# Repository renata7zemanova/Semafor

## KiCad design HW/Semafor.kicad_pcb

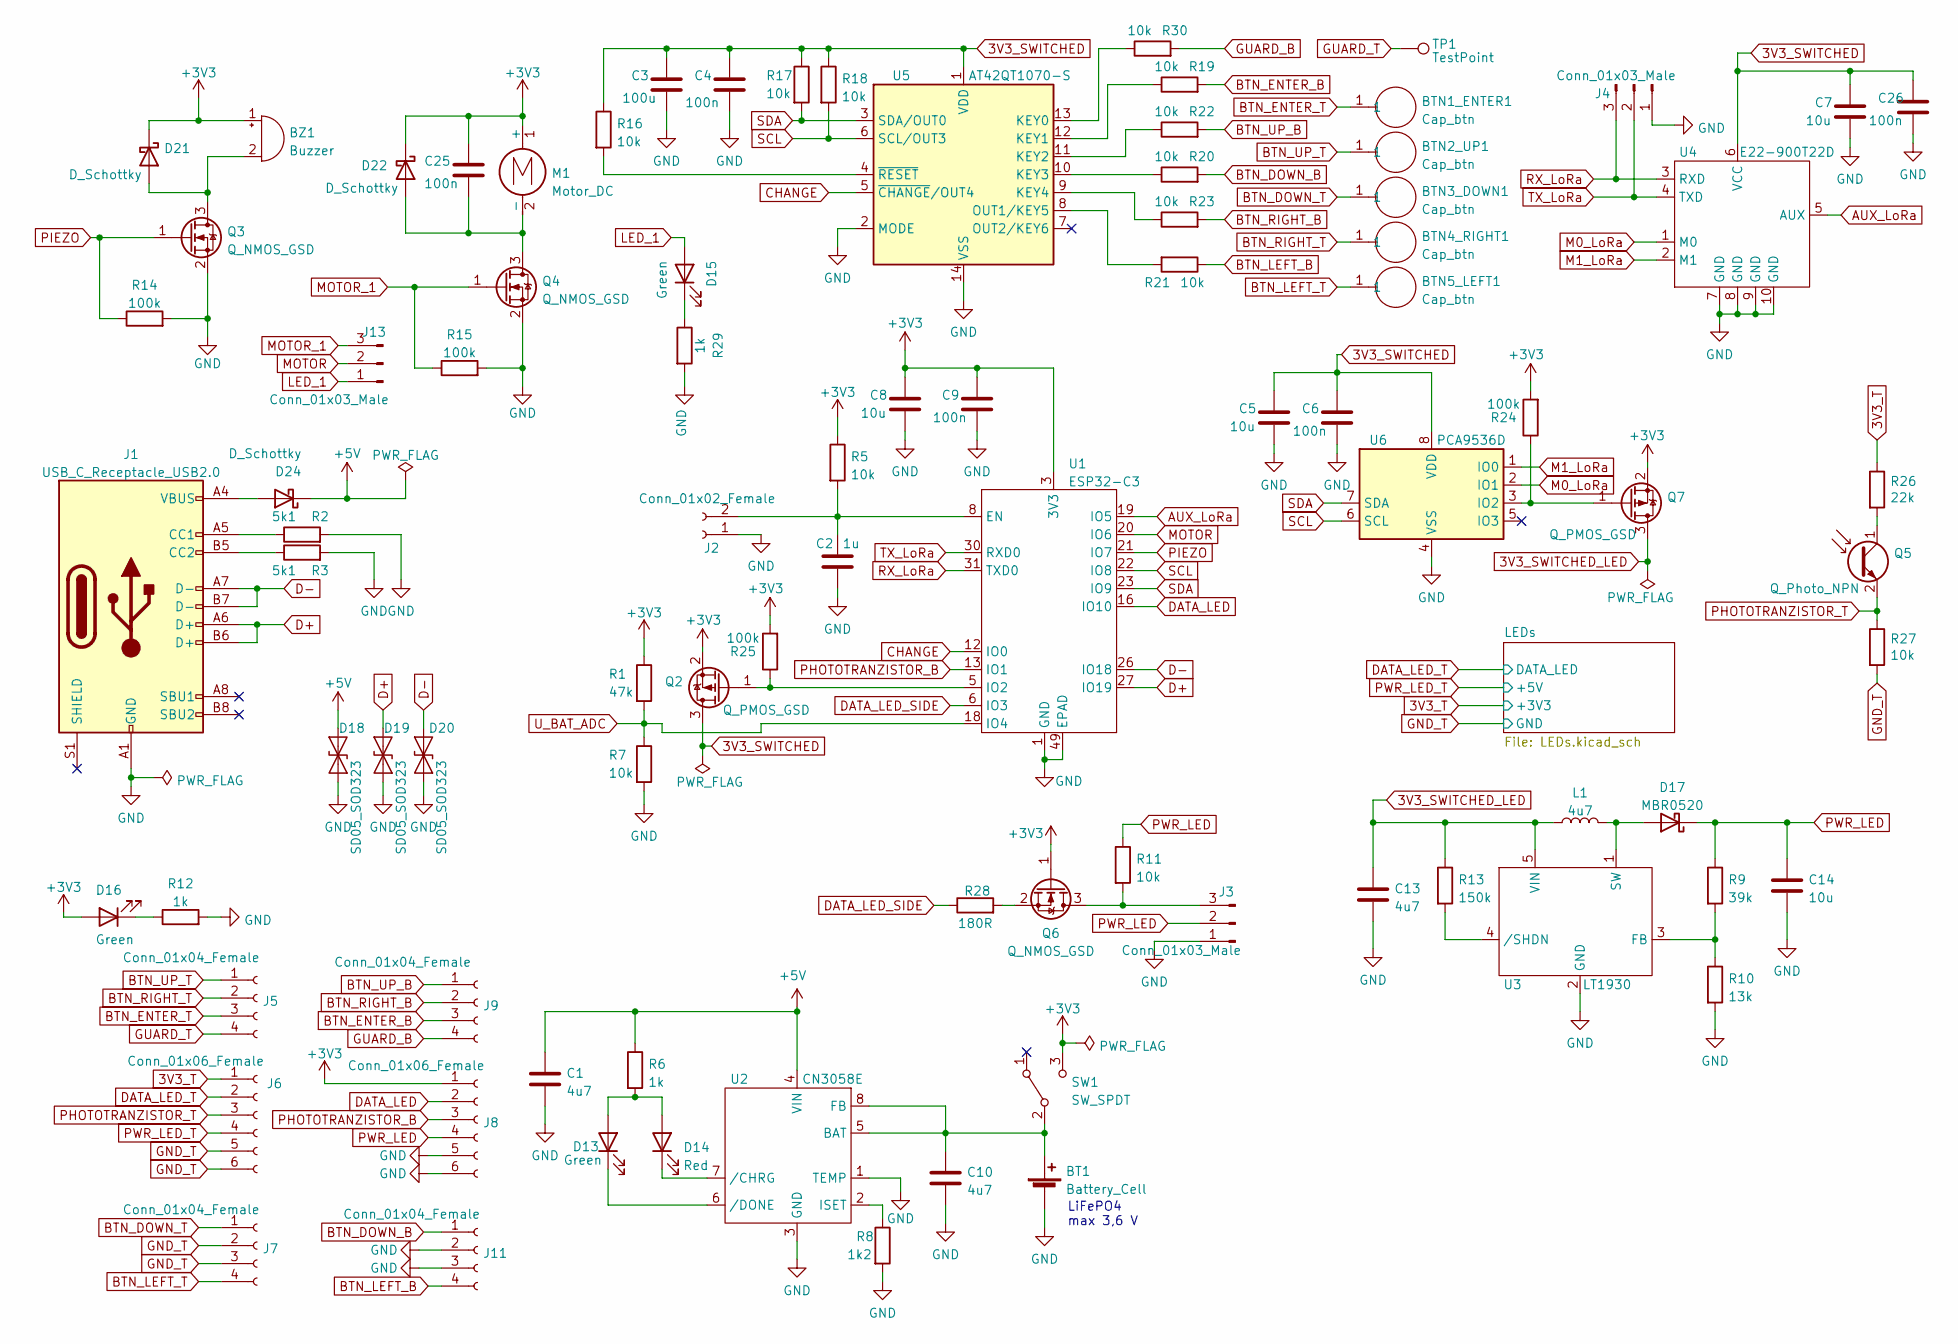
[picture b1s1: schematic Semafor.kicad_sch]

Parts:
BT1: Battery_Cell; battery_dock; LCSC ručně
BTN1_ENTER1: Cap_btn; Cap_btn_4x4
BTN2_UP1, BTN3_DOWN1, BTN4_RIGHT1, BTN5_LEFT1: Cap_btn; Cap_btn_1,6x1,6
BZ1: Buzzer; PIEZO; LCSC ručně
C1, C10, C13: 4u7; C_0805_2012Metric; LCSC C1779
C2: 1u; C_0805_2012Metric; LCSC C28323
C3: 100u; C_0805_2012Metric; LCSC ručně
C4, C6, C9, C25, C26: 100n; C_0603_1608Metric; LCSC C14663
C5, C7, C8, C14: 10u; C_0805_2012Metric; LCSC C15850
D13, D15, D16: Green; LED_0603_1608Metric; LCSC C965805
D14: Red; LED_0603_1608Metric; LCSC C965799
D17: MBR0520; D_SOD-123; LCSC C77335
D18, D19, D20: SD05_SOD323; D_SOD-323; LCSC C3002993
D21, D22, D24: D_Schottky; D_SOD-123; LCSC C2909923
J1: USB_C_Receptacle_USB2.0; USB_C_Receptacle_HRO_TYPE-C-31-M-12; LCSC C136423
J2: Conn_01x02_Female; PinSocket_1x02_P1.27mm_Vertical; LCSC ručně
J3, J4, J13: Conn_01x03_Male; PinSocket_1x03_P2.54mm_Vertical; LCSC ručně
J5, J7, J9, J11: Conn_01x04_Female; PinHeader_1x04_P2.54mm_Vertical; LCSC ručně
J6, J8: Conn_01x06_Female; PinSocket_1x06_P2.54mm_Vertical; LCSC ručně
L1: 4u7; L_CDRH3D18; LCSC C167273
M1: Motor_DC; PinHeader_1x02_P2.54mm_Vertical; LCSC C2891560
Q2, Q7: Q_PMOS_GSD; SOT-23; LCSC C10487
Q3, Q4, Q6: Q_NMOS_GSD; SOT-23; LCSC C8545
Q5: Q_Photo_NPN; SMD,3.5x2.8x1.9mm; JLCPCB_CORRECTION 0;0;0
R1: 47k; R_0603_1608Metric; LCSC C25819
R2, R3: 5k1; R_0402_1005Metric; LCSC C25905
R5, R7, R11, R16, R17, R18, R19, R20, R21, R22, R23, R30: 10k; R_0603_1608Metric; LCSC C25804
R6, R12, R29: 1k; R_0603_1608Metric; LCSC C21190
R8: 1k2; R_0603_1608Metric; LCSC C22765
R9: 39k; R_0603_1608Metric; LCSC C23153
R10: 13k; R_0603_1608Metric; LCSC C22797
R13: 150k; R_0603_1608Metric; LCSC C22807
R14, R15, R24, R25: 100k; R_0603_1608Metric; LCSC C25803
R26: 22k; R_0402_1005Metric; JLCPCB_CORRECTION 0;0;0
R27: 10k; R_0402_1005Metric; JLCPCB_CORRECTION 0;0;0
R28: 180R; R_0603_1608Metric; LCSC C22828
SW1: SW_SPDT; BTN_1101M2S2AV2QE2; LCSC C221537
TP1: TestPoint; TestPoint_Pad_D2.0mm
U1: ESP32-C3; LCSC C2838502
U2: CN3058E; SOP-8_3.76x4.96mm_P1.27mm; LCSC C112011
U3: LT1930; SOT-23-5; LCSC C579930
U4: E22-900T22D; LCSC ručně
U5: AT42QT1070-S; SOIC-14_3.9x8.7mm_P1.27mm; LCSC ručně
U6: PCA9536D; SOIC-8_3.9x4.9mm_P1.27mm; LCSC C129522

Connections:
3V3_SWITCHED: C3.1, C4.1, C5.1, C6.1, C7.1, C26.1, Q2.3 (D), R16.1, R17.1, R18.1, U4.6 (VCC), U5.1 (VDD), U6.8 (VDD)
3V3_SWITCHED_LED: C13.1, L1.1, Q7.3 (D), R13.1, U3.5 (VIN)
3V3_T: J6.1, R26.1; also elsewhere on the board
+3V3: BZ1.1 (-), C8.1, C9.1, C25.1, D16.2 (A), D21.1 (K), D22.1 (K), J8.1, M1.1 (+), Q2.2 (S), Q6.1 (G), Q7.2 (S), R1.1, R5.1, R24.2, R25.2, SW1.3 (C), U1.3 (3V3)
+5V: C1.1, D18.2 (A2), D24.1 (K), R6.1, U2.4 (VIN)
AUX_LoRa: U1.19 (IO5), U4.5 (AUX)
BTN_DOWN_B: J11.1, R20.2
BTN_DOWN_T: BTN3_DOWN1.1, J7.1
BTN_ENTER_B: J9.3, R19.2
BTN_ENTER_T: BTN1_ENTER1.1, J5.3
BTN_LEFT_B: J11.4, R21.1
BTN_LEFT_T: BTN5_LEFT1.1, J7.4
BTN_RIGHT_B: J9.2, R23.2
BTN_RIGHT_T: BTN4_RIGHT1.1, J5.2
BTN_UP_B: J9.1, R22.2
BTN_UP_T: BTN2_UP1.1, J5.1
CHANGE: U1.12 (IO0), U5.5 (~CHANGE/OUT4)
D+: D19.2 (A2), J1.A6 (D+), J1.B6 (D+), U1.27 (IO19)
D-: D20.2 (A2), J1.A7 (D-), J1.B7 (D-), U1.26 (IO18)
DATA_LED: J8.2, U1.16 (IO10)
DATA_LED_SIDE: R28.1, U1.6 (IO3)
DATA_LED_T: J6.2; also elsewhere on the board
GND: BT1.2 (-), C1.2, C2.2, C3.2, C4.2, C5.2, C6.2, C7.2, C8.2, C9.2, C10.2, C13.2, C14.2, C26.2, D18.1 (A1), D19.1 (A1), D20.1 (A1), J1.A1 (GND), J1.A12 (GND), J1.B1 (GND), J1.B12 (GND), J2.1, J3.1, J4.1, J8.5, J8.6, J11.2, J11.3, Q3.2 (S), Q4.2 (S), R2.2, R3.2, R7.2, R8.2, R10.2, R12.2, R14.2, R15.2, R29.2, U1.1 (GND), U1.2 (GND), U1.11 (GND), U1.14 (GND), U1.36 (GND), U1.37 (GND), U1.38 (GND), U1.39 (GND), U1.40 (GND), U1.41 (GND), U1.42 (GND), U1.43 (GND), U1.44 (GND), U1.45 (GND), U1.46 (GND), U1.47 (GND), U1.48 (GND), U1.49 (EPAD), U1.50 (GND), U1.51 (GND), U1.52 (GND), U1.53 (GND), U2.1 (TEMP), U2.3 (GND), U3.2 (GND), U4.7 (GND), U4.8 (GND), U4.9 (GND), U4.10 (GND), U5.2 (MODE), U5.14 (VSS), U6.4 (VSS)
GND_T: J6.5, J6.6, J7.2, J7.3, R27.2; also elsewhere on the board
GUARD_B: J9.4, R30.2
GUARD_T: J5.4, TP1.1
LED_1: D15.2 (A), J13.1
M0_LoRa: U4.1 (M0), U6.2 (IO1)
M1_LoRa: U4.2 (M1), U6.1 (IO0)
MOTOR: J13.2, U1.20 (IO6)
MOTOR_1: J13.3, Q4.1 (G), R15.1
unnamed: BT1.1 (+), C10.1, SW1.2 (B), U2.5 (BAT), U2.8 (FB)
unnamed: BZ1.2 (+), D21.2 (A), Q3.3 (D)
unnamed: C2.1, J2.2, R5.2, U1.8 (EN)
unnamed: C25.2, D22.2 (A), M1.2 (-), Q4.3 (D)
unnamed: D13.1 (K), U2.6 (/DONE)
unnamed: D13.2 (A), D14.2 (A), R6.2
unnamed: D14.1 (K), U2.7 (/CHRG)
unnamed: D15.1 (K), R29.1
unnamed: D16.1 (K), R12.1
unnamed: D17.2 (A), L1.2, U3.1 (SW)
unnamed: D24.2 (A), J1.A4 (VBUS), J1.A9 (VBUS), J1.B4 (VBUS), J1.B9 (VBUS)
unnamed: J1.A5 (CC1), R2.1
unnamed: J1.B5 (CC2), R3.1
unnamed: J3.3, Q6.3 (D), R11.2
unnamed: Q2.1 (G), R25.1, U1.5 (IO2)
unnamed: Q5.1 (C), R26.2
unnamed: Q6.2 (S), R28.2
unnamed: Q7.1 (G), R24.1, U6.3 (IO2)
unnamed: R8.1, U2.2 (ISET)
unnamed: R9.2, R10.1, U3.3 (FB)
unnamed: R13.2, U3.4 (/SHDN)
unnamed: R16.2, U5.4 (~RESET)
unnamed: R19.1, U5.12 (KEY1)
unnamed: R20.1, U5.10 (KEY3)
unnamed: R21.2, U5.8 (OUT1/KEY5)
unnamed: R22.1, U5.11 (KEY2)
unnamed: R23.1, U5.9 (KEY4)
unnamed: R30.1, U5.13 (KEY0)
PHOTOTRANZISTOR_B: J8.3, U1.13 (IO1)
PHOTOTRANZISTOR_T: J6.3, Q5.2 (E), R27.1
PIEZO: Q3.1 (G), R14.1, U1.21 (IO7)
PWR_LED: C14.1, D17.1 (K), J3.2, J8.4, R9.1, R11.1
PWR_LED_T: J6.4; also elsewhere on the board
RX_LoRa: J4.3, U1.31 (TXD0), U4.3 (RXD)
SCL: R18.2, U1.22 (IO8), U5.6 (SCL/OUT3), U6.6 (SCL)
SDA: R17.2, U1.23 (IO9), U5.3 (SDA/OUT0), U6.7 (SDA)
TX_LoRa: J4.2, U1.30 (RXD0), U4.4 (TXD)
U_BAT_ADC: R1.2, R7.1, U1.18 (IO4)

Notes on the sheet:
LiFePO4 max 3,6 V

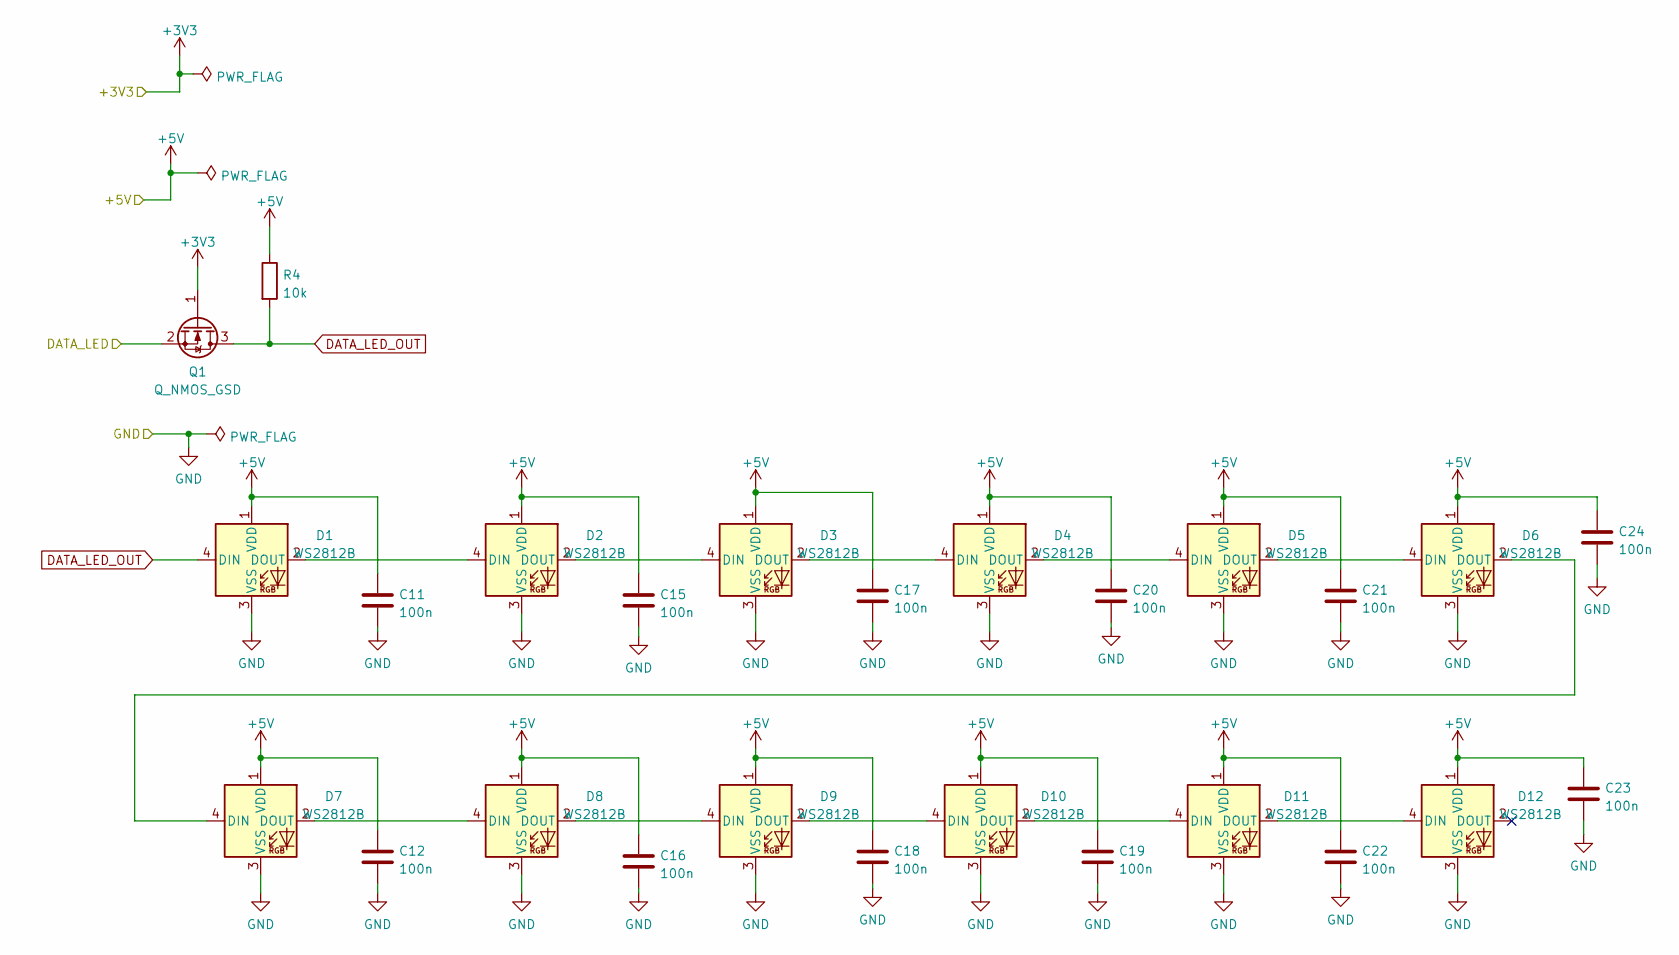
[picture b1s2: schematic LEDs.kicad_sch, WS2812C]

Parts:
C11, C12, C15, C16, C17, C18, C19, C20, C21, C22, C23, C24: 100n; C_0603_1608Metric; LCSC C14663
D1, D2, D3, D4, D5, D6, D7, D8, D9, D10, D11, D12: WS2812B; LED_WS2812B_PLCC4_5.0x5.0mm_P3.2mm; LCSC C2761796
Q1: Q_NMOS_GSD; SOT-23; LCSC C8545
R4: 10k; R_0603_1608Metric; LCSC C25804

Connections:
3V3_T: Q1.1 (G); also elsewhere on the board
DATA_LED_OUT: D1.4 (DIN), Q1.3 (D), R4.2
DATA_LED_T: Q1.2 (S); also elsewhere on the board
GND_T: C11.2, C12.2, C15.2, C16.2, C17.2, C18.2, C19.2, C20.2, C21.2, C22.2, C23.2, C24.2, D1.3 (VSS), D2.3 (VSS), D3.3 (VSS), D4.3 (VSS), D5.3 (VSS), D6.3 (VSS), D7.3 (VSS), D8.3 (VSS), D9.3 (VSS), D10.3 (VSS), D11.3 (VSS), D12.3 (VSS); also elsewhere on the board
unnamed: D1.2 (DOUT), D2.4 (DIN)
unnamed: D2.2 (DOUT), D3.4 (DIN)
unnamed: D3.2 (DOUT), D4.4 (DIN)
unnamed: D4.2 (DOUT), D5.4 (DIN)
unnamed: D5.2 (DOUT), D6.4 (DIN)
unnamed: D6.2 (DOUT), D7.4 (DIN)
unnamed: D7.2 (DOUT), D8.4 (DIN)
unnamed: D8.2 (DOUT), D9.4 (DIN)
unnamed: D10.2 (DOUT), D11.4 (DIN)
unnamed: D9.2 (DOUT), D10.4 (DIN)
unnamed: D11.2 (DOUT), D12.4 (DIN)
PWR_LED_T: C11.1, C12.1, C15.1, C16.1, C17.1, C18.1, C19.1, C20.1, C21.1, C22.1, C23.1, C24.1, D1.1 (VDD), D2.1 (VDD), D3.1 (VDD), D4.1 (VDD), D5.1 (VDD), D6.1 (VDD), D7.1 (VDD), D8.1 (VDD), D9.1 (VDD), D10.1 (VDD), D11.1 (VDD), D12.1 (VDD), R4.1; also elsewhere on the board

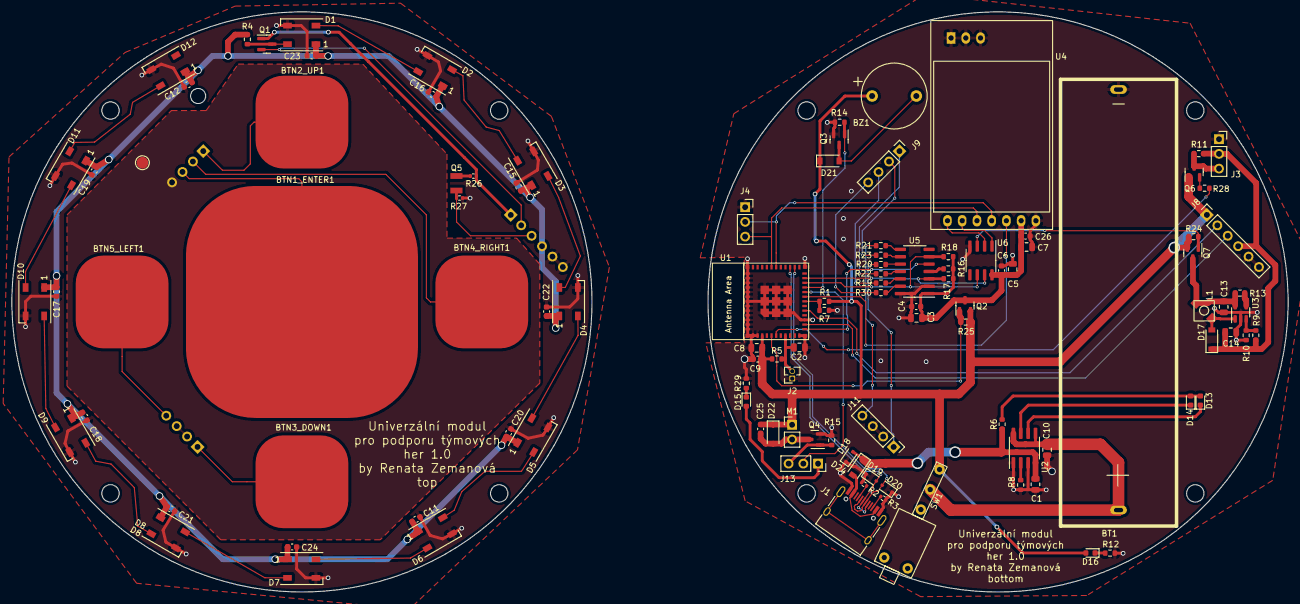
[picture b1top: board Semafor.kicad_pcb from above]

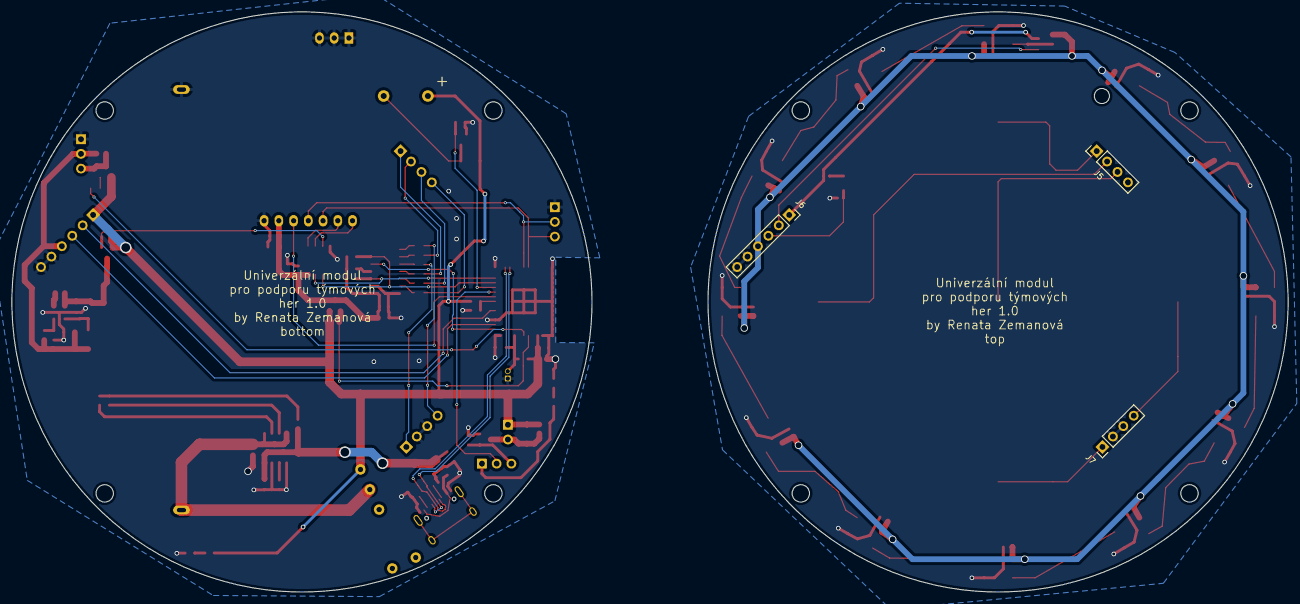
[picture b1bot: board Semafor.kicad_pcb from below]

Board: 2 copper layers, 220.0 x 100.0 mm, 114 parts (3 on the bottom side), 81 nets.

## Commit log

2022-10-26 template for text of thesis
2022-10-26 update gitignore
2022-10-27 add new symbol and package of ESP32-C3
2022-10-27 add footprint of battery dock
2022-10-27 start drawing schematic and PCB - LEDs, buttons, battery dock, ESP32-C3
2022-10-31 add symbol of CN3058E to library
2022-11-02 start writing, describing the selection of parts of the circuit
2022-11-02 add symbol of step up LT1930
2022-11-02 schematic with MCU, USB-C, LEDs, buttons, level shifter and step up
2022-11-02 add text about charger and some comments
2022-11-02 add peripherial for ESP32-C3, add temporary package of switch and inductor, add package of MOS
2022-11-02 basic placing units
2022-11-03 add package of inductor to library
2022-11-03 change package of inductor + add LSCS code
2022-11-07 change value of inductor, update PCB, repair connection step up of pin /SHDN, delete capacitors from ESP32
2022-11-07 add package and symbol of LoRa module E22-900T22D
2022-11-07 update symbol of LoRa module
2022-11-07 update symbol ESP32-C3, add capacitors to WS2812C, add transils to USB
2022-11-08 add piezo, vibration motor
2022-11-08 add USB_plug
2022-11-09 update footprint of battery dock
2022-11-09 add capacitive touch buttons and converter AT42QT1070
2022-11-09 update footprints of capacitive touch buttons, PCB
    place capacitive buttons, LEDs, LoRa module, battery pack
2022-11-09 add text about vibrate motor, converter for capacitive touch buttons AT42QT1070
2022-11-09 add some datasheets, add diodes to USBs
2022-11-12 text about PCB - capacitive buttons, LEDs WS2812C, wireless communication
2022-11-17 text about ZigBee, microcontroller, delete picture (Wilsonovo proudové zrcadlo), add info about LT1930
2022-11-17 change datasheet WS2812C, add datasheet LT1930, repair voltage on pin FB of LT1930
2022-11-19 routing PCB - LEDs
2022-11-19 text about charger, buttons
2022-11-19 add text about buttons
2022-11-30 add task and front-page
2022-11-30 add information about me
2022-12-05 repair title-page
2022-12-05 do correction in text, add text about LiFePO4
2022-12-05 add text about batteries
2022-12-28 text separate to more sections, add text about LoRa
2022-12-28 add fill of description field
2022-12-30 add voltage reference
2022-12-30 add text about microcontroler, delete introduction, add some shortcuts, delete some attachments
2022-12-30 add block diagram, change some titles
2022-12-31 add final block diagram, add text about power LED and sound signalization
2022-12-31 add datasheet, change engagement at CN3058E of TEMP
2023-01-01 repair text I2C, add text about bettery charger, add new title pages
2023-01-01 add text about diode, inductor and piezo, delete text about PCB
2023-01-01 repair shottky diodes
2023-01-02 add text about shottky diodes, add block diagram of MCU and text about MCU, update pdf with task, repair mistakes and add some text to introduction and conclusion
2023-01-02 add block diagram to side dishes, add abstract and keywords
2023-01-02 repair mistakes in schematic, add switched supply voltage to LoRa, LEDs and converter for capacitive buttons
2023-01-02 add images, repair some images, add side dishes, delete mistakes in charge module
2023-01-03 change letter type in block diagram, add text to conclusion, bibliography sorted aplhabetically, repair mistakes
2023-01-03 add text about Sigfox, add text to introduction
2023-01-03 after "vlna"
2023-01-03 update PCB
2023-01-09 make presentation, add some images for presentation
2023-01-18 repair ERC errors
2023-01-18 routing ESP and charger
2023-01-28 routing
2023-02-03 routing done
2023-02-03 add some codes for assembly byJLCPCB
2023-02-05 add title of PCB
2023-02-05 add LCSC codes for assembly
2023-02-06 repair fill zones
2023-02-06 add fabrication files
2023-02-06 reduction dimensions of PCB + routing, update fabrication files
2023-02-15 make folder for HW v0.0
2023-02-16 add folder FW to project with ESP_IDF, add gitignore for ESP-IDF
2023-02-17 make new project, add libraries
2023-02-23 new FW project with platformio (from bachelor thesis)
2023-02-26 prepair structure of FW code
2023-02-27 functions for LEDs
2023-02-28 add functions for battery and button
2023-03-01 prepare funcitions for LoRa, add library for AT42QT1070-S
2023-03-01 add function for motor, piezo, delete old functions for capacitive buttons, change structure and using structure for LED
2023-03-07 update FW, add functions of WiFi
2023-03-07 preparing form for silicone transparent cover
2023-03-07 add web file
2023-03-10 add libraries for LoRa and write test code
2023-03-16 repair mistake with LoRa and change board on ESP32-C3
2023-03-17 add text about LoRa and PCB
2023-03-17 add text about games for Semafor
2023-03-20 repair libraries, substitude SmartLeds by NeoPixel
2023-03-22 separate lib to .h and .cpp
2023-03-22 add part of function logic, repair lib for web
2023-03-23 add some function logic, start write game odpocitavadlo
2023-03-27 sw for testing prototype PCB
2023-03-30 add text about testing prototype PCB
2023-03-31 change Semestral thesis to Diploma thesis (title page, task, settings,....)
2023-04-04 repair library AtTouch
2023-04-04 AtTouch library back - other way of inicialization
2023-04-05 create my library for chip for capacitive buttons AT42QT1070
2023-04-11 text about testing capacitive buttons and chip AT42QT1070
2023-04-12 add function is_some_btn_touched, changes in web files (it doesnt work)
2023-04-12 repair mistakes from prototype PCB
2023-04-12 add phototransistor and connector for programmable LEDs (on side)
2023-04-14 add webserver, start web page
2023-04-14 add working webpage + processing form
2023-04-18 start drawing small version of Module, draw stepup as per datasheet
2023-04-18 change all library AT42QT1070.h - better detection of touch
2023-04-18 continue routing
2023-04-19 repairs, alterations and hints from to webserver and work with it
2023-04-19 done routing of version 1.0
2023-04-20 charging LEDs place to PCB bottom
2023-04-20 touching buttons is certain with multitouch
2023-04-20 repair function find_active_key and rename (get_raw_data_btn), add function is_touched_some_btn and tick_for_buttons to lib
2023-04-21 game odpocitavadlo: time countdown works
2023-04-21 basic game Semafor is ready, add 2 versions of Vabnicka
2023-04-23 add text about soldering, FW - AT42QT1070, LEDs, battery
2023-04-23 add function toggle all LEDs
2023-04-24 repair mistakes and preparing for 2 PCBs (sandwich)
2023-04-24 routed top PCB (with buttons, LEDs and phototransistor)
2023-04-24 2 PCB version of Semafor done
2023-04-24 rotate Q2
2023-04-24 change some routing tracks
2023-04-24 replace labels
2023-04-24 start writing sharing settings - it doesnt work
2023-04-25 add sending and receiving settings
2023-04-25 repair vibration, delays to metronome, add ESP32-WROOM platform
2023-04-26 add permanently saving - Preferences
2023-04-26 add slide switch for power on, change guard zone around buttons
2023-04-26 add 3D models of my gadgets
2023-04-26 changes for better EMC, change thickness of tracks, change position of pinheads
2023-04-27 add thermals to top PCB, solve thombstoning
2023-04-27 save fab for v0.0, generate fab for v1.0
2023-04-27 add via to step up output C
2023-04-27 add text about water resistance + user manual
2023-04-28 prepare separate boards for fab
2023-04-28 generate fab for top and bottom PCB, delete fab for both of PCB together
2023-04-28 change positions of some parts on bottom PCB - prepare for fab
2023-04-30 text about final version of PCB
2023-05-02 add 3D model of piezo
2023-05-03 add block schematic with FW, add text about silicone cover
2023-05-05 add model of silicone mould
2023-05-05 add text about cover and about game modes
2023-05-05 add some parts to new folder - "soucastky", add long pinheaders
2023-05-05 change 3D parts .wrl to .step
2023-05-05 add saving games from configuration, add sending configuration to other Semafors
2023-05-07 first proofreading
2023-05-07 add 3D model of power switch
2023-05-07 add 3d model of power switch to PCB
2023-05-07 make backup of v1.0 with 3D models of some parts
2023-05-09 first proofreading continued, add images and block diagrams
2023-05-10 add photos of prototype PCB
2023-05-12 second revision of the text
2023-05-12 add attachments
2023-05-12 repair text about FW
2023-05-12 use "vlna"
2023-05-12 add examples on using Universal module in camp games
2023-05-15 update FW for version v1.0.
2023-05-15 text - add image of configuration web page
2023-05-15 add 3D models of cover
2023-05-15 create game "semafor", update game "odpocitavadlo"
2023-05-15 generate 3MF and STL of cover for printing
2023-05-15 games "odpocitavadlo" and "vabnicka: are ready
2023-05-16 working on phototransistor and battery measurement, sending settings is working
2023-05-16 text about cover and assembly
2023-05-16 update description field
2023-05-18 add photos with complete Universal module
2023-05-21 final text
2023-05-22 final version of FW
2023-05-30 first version of presentation
2023-06-06 final version of presentation - add questions and answers for opponent of the thesis
2023-06-06 final presentation - new pdf
2023-06-06 add sound to game "odpocitavadlo"
